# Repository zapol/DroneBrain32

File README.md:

DroneBrain32
============

Control board for autonomous drone, mostly compatible with OpenLRS32

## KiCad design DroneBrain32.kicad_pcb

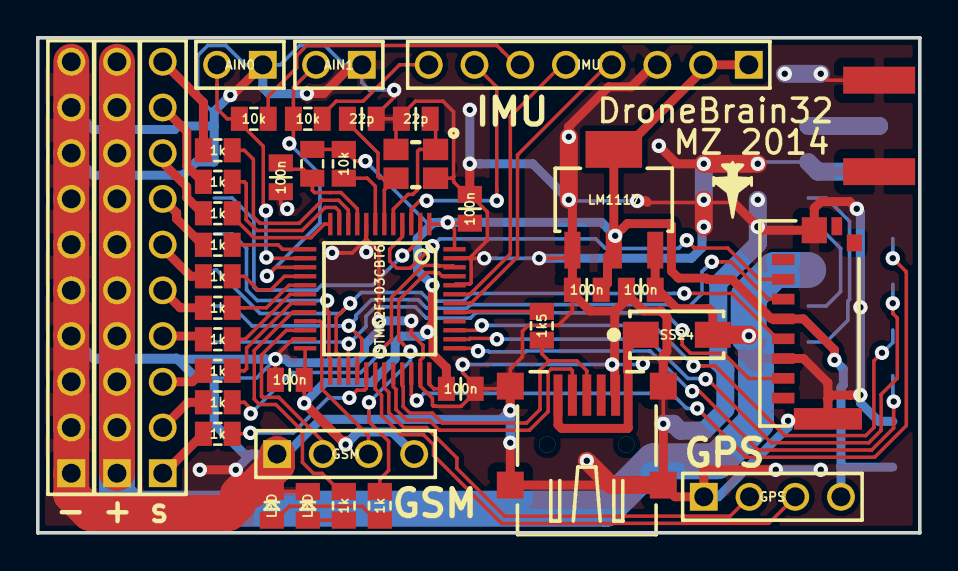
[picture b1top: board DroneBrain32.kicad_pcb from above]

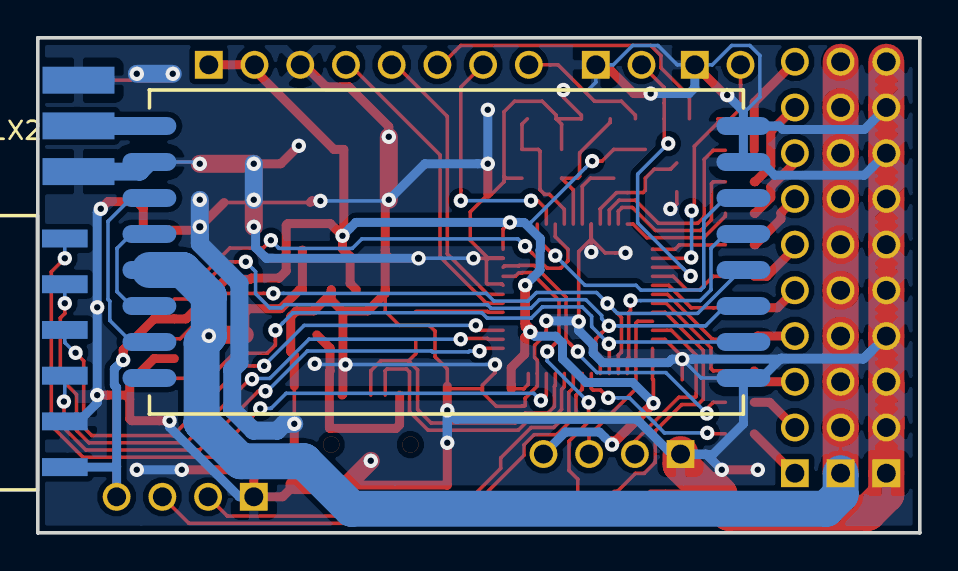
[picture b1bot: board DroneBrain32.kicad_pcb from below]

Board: 2 copper layers, 49.0 x 27.5 mm, 44 parts (3 on the bottom side), 59 nets.

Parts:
C1, C2: 22p; C0805
C4, C5, C6, C7, C8, C9: 100n; C0805
D1, D2: LED; D0805
D3: SS24; SMA
J1: HEADER1X2; CON_SMA-Edge
J2: AIN0; HEADER1x2V
J3: JTAG; HEADER1x6EF
J4: AIN1; HEADER1x2V
J5: GPS; HEADER1x4V
J6: USB-MINI-A; USB-A-MINI
J7: IMU; HEADER1x8V
J8, J9, J10: HEADER1X10; HEADER1x10V
J11: GSM; HEADER1x4V
L1: ferrite bead; R0805
R1, R3, R4: 10k; R0805
R2, R6, R7, R8, R9, R10, R11, R12, R13, R14, R15, R16: 1k; R0805
R5: 1k5; R0805
U1: RFM23BP
U2: STM32F103CBT6; LQFP48_L
U3: MICROSD; MicroSD_MOLEX_47309-3351
U4: LM1117; SOT223
X1: XT324

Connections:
+3V3: C4.2, C5.2, C6.2, C9.2, J3.1, J5.4, J7.1, J7.2, J11.4, L1.1, R1.1, U2.1, U2.24, U2.36, U2.48, U3.4, U4.2, U4.4
+5V: C8.2, D3.2, J9.1, J9.2, J9.3, J9.4, J9.5, J9.6, J9.7, J9.8, J9.9, J9.10, U1.5, U4.3
/CH1: R7.1, U2.10
/CH2: R8.1, U2.11
/CH3: R9.1, U2.12
/CH4: R10.1, U2.13
/CH5: R11.1, U2.16
/CH6: R12.1, U2.17
/CH7: R13.1, U2.18
/CH8: R14.1, U2.19
/IMU_DRDY: J7.8, R4.1
/IMU_FSYNC: J7.6, R3.1
/IMU_INTA: J7.7, U2.3
/IMU_SCL: J7.4, U2.42
/IMU_SDA: J7.5, U2.43
/LED0: R2.2, U2.20
/LED1: R6.2, U2.45
/MISO: U1.10, U2.27, U3.7
/MOSI: U1.11, U2.28, U3.3
/NIRQ_RFM: U1.14, U2.2
/NRST: R1.2, U2.7
/NSEL_RFM: U1.13, U2.25
/NSEL_SD: U2.4, U3.2
/PPM: R16.1, U2.29
/RSSI: R15.1, U2.46
/Rx: J5.2, U2.31
/SCK: U1.12, U2.26, U3.5
/SCL: J11.3, U2.21
/SDA: J11.2, U2.22
/TCK: J3.3, U2.37
/TDI: J3.5, U2.38
/TDO: J3.4, U2.39
/TMS: J3.6, U2.34
/Tx: J5.3, U2.30
/USB_DM: J6.2, U2.32
/USB_DP: J6.3, R5.1, U2.33
/USB_PU: R5.2, U2.41
GND: C1.1, C2.1, C4.1, C5.1, C6.1, C7.1, C8.1, C9.1, D1.2, D2.2, J1.1, J2.1, J3.2, J4.1, J5.1, J6.5, J6.6, J6.7, J6.8, J6.9, J7.3, J8.1, J8.2, J8.3, J8.4, J8.5, J8.6, J8.7, J8.8, J8.9, J8.10, J11.1, U1.2, U1.9, U1.15, U1.16, U2.8, U2.23, U2.35, U2.44, U2.47, U3.6, U3.11, U3.12, U4.1, X1.2, X1.4
unnamed: C1.2, U2.5, X1.1
unnamed: C2.2, U2.6, X1.3
unnamed: C7.2, L1.2, U2.9
unnamed: D1.1, R2.1
unnamed: D2.1, R6.1
unnamed: D3.1, J6.1
unnamed: J1.2, U1.1
unnamed: J2.2, R3.2, U2.14
unnamed: J4.2, R4.2, U2.15
unnamed: J10.1, R16.2
unnamed: J10.2, R15.2
unnamed: J10.3, R14.2
unnamed: J10.4, R13.2
unnamed: J10.5, R12.2
unnamed: J10.6, R11.2
unnamed: J10.7, R10.2
unnamed: J10.8, R9.2
unnamed: J10.9, R8.2
unnamed: J10.10, R7.2
unnamed: U1.3, U1.7
unnamed: U1.4, U1.6

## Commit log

2014-12-01 Schematic initial version
2014-12-01 Continuing schematic
2014-12-02 Finished schematic, started placement.
2014-12-02 Continuing component placement, started routing
2014-12-03 Finished routing - first iteration
2014-12-03 Showing unconnected when all is connected
2014-12-04 Finished board.
2014-12-04 Fixed vias for EC production
2014-12-04 Added decals
2014-12-05 Fixed incorrect RFM23BP SPI pins assignment
2014-12-05 Improved GND
2014-12-05 Added 3D components - might have troubles with paths
2021-11-25 Update library references
